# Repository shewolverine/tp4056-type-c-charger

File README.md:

# Charger Module
This module charges lithium batteries up to 1 cell.

## Used ICs
- TP4056
- DW01A
- FS8205A

 ### Note
 This PCB designed as one layer version and two layer version.

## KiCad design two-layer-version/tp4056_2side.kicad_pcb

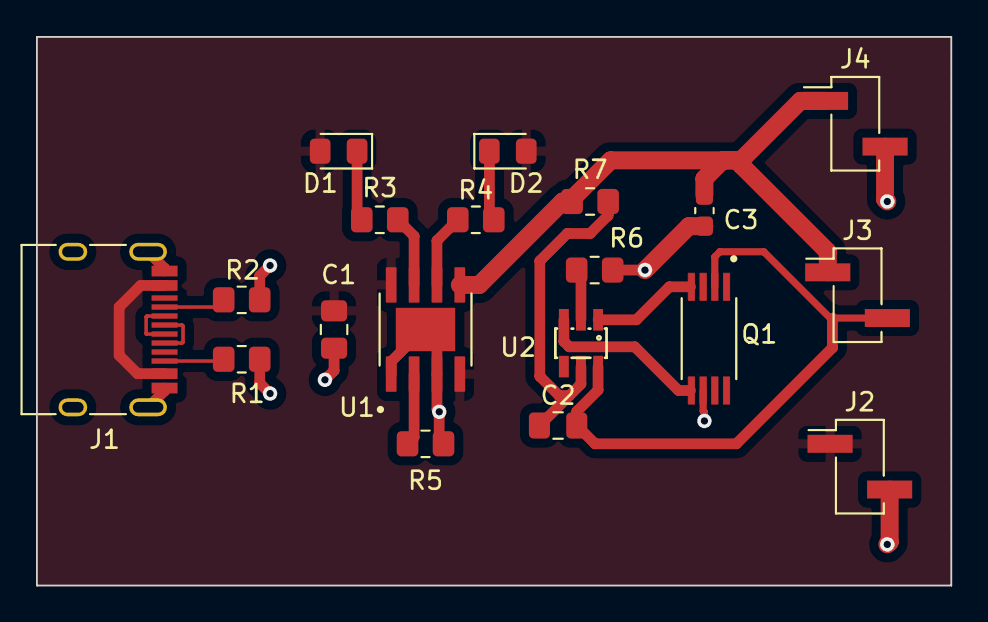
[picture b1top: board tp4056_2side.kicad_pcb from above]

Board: 2 copper layers, 50.8 x 30.5 mm, 19 parts (0 on the bottom side), 17 nets.

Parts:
C1, C2: 100n; C_0805_2012Metric_Pad1.18x1.45mm_HandSolder
C3: 10u; C_0603_1608Metric_Pad1.08x0.95mm_HandSolder
D1, D2: LED; LED_0805_2012Metric_Pad1.15x1.40mm_HandSolder
J1: USB_C_Receptacle_USB2.0; USB_C_Receptacle_HRO_TYPE-C-31-M-12
J2: +-; PinHeader_1x02_P2.54mm_Vertical_SMD_Pin1Left
J3: 1B+2B-; PinHeader_1x02_P2.54mm_Vertical_SMD_Pin1Left
J4: 1OUT+2OUT-; PinHeader_1x02_P2.54mm_Vertical_SMD_Pin1Left
Q1: FS8205A; SOP65P640X120-8N
R1, R2: 5k1; R_0805_2012Metric_Pad1.20x1.40mm_HandSolder
R3, R4, R6: 1k; R_0805_2012Metric_Pad1.20x1.40mm_HandSolder
R5: 1k2; R_0805_2012Metric_Pad1.20x1.40mm_HandSolder
R7: 100; R_0805_2012Metric_Pad1.20x1.40mm_HandSolder
U1: TP4056; SOP127P600X175-9N
U2: DW01A; SOT23-6

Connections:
+5V: C1.1, D1.2 (A), D2.2 (A), J1.A4 (VBUS), J1.A9 (VBUS), J1.B4 (VBUS), J1.B9 (VBUS), J2.1, U1.4 (VCC), U1.8 (CE)
GND: C1.2, C3.2, J1.A1 (GND), J1.A12 (GND), J1.B1 (GND), J1.B12 (GND), J1.S1 (SHIELD), J2.2, J4.2, Q1.6, R1.2, R2.2, R5.2, R6.2, U1.1 (TEMP), U1.3 (GND), U1.9 (EP)
unnamed: D1.1 (K), R3.2
unnamed: D2.1 (K), R4.2
unnamed: J1.A5 (CC1), R2.1
unnamed: J1.B5 (CC2), R1.1
unnamed: J1.A6 (D+), J1.B6 (D+)
unnamed: J1.A7 (D-), J1.B7 (D-)
unnamed: C3.1, J3.1, J4.1, R7.2, U1.5 (BAT)
unnamed: C2.2, J3.2, Q1.2, U2.6 (GND)
unnamed: R5.1, U1.2 (PROG)
unnamed: R3.1, U1.7 (~CHRG)
unnamed: R4.1, U1.6 (~STDBY)
unnamed: R6.1, U2.2 (CS)
unnamed: Q1.5, U2.3 (OC)
unnamed: Q1.4, U2.1 (OD)
unnamed: C2.1, R7.1, U2.5 (VCC)

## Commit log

2023-11-06 readme file added
2023-12-12 2-layer board designed
2023-12-12 README modified
